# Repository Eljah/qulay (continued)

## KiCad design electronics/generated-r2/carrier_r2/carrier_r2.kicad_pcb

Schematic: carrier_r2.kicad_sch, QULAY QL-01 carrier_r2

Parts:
C1, C2, C3: 100n X7R; C0603
C4: 10u X7R 6.3V; C0603
J1: EXTERNAL_3V3_FUSED_1A; H2
J2: ENCODER_BANK_0; H6
J3: ENCODER_BANK_1; H6
J4: ENCODER_BANK_2; H6
J5: ENCODER_BANK_3; H6
J6: ADXL355_MODULE; H7
J7: ODOMETER_3V3_ONLY; H4
J8: ADC_BANK_FANOUT; H10
J9: INTERLOCK_GND_LIFT_PG_REMOTE_PULLUP; H4
Q1: MMBT3904; SOT23
R1, R2, R3, R4, R5, R6, R7, R8: 10k default-CS-high; R0603
R9, R11: 10k; R0603
R10, R13, R14: 100k; R0603
R12: 100k wire-open-low; R0603
R15, R16, R17, R18: 47R source termination; R0603
U1: Raspberry_Pi_Pico_USB_powered; PICO40
U2, U3: SN74LVC244APWR; TSSOP20
U4: SN74LVC125AD_IOFF; SOIC14

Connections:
ADC_CS0: J8.6 (ADC_CS0), R5.2 (ADC_CS0), U3.18 (ADC_CS0)
ADC_CS1: J8.7 (ADC_CS1), R6.2 (ADC_CS1), U3.16 (ADC_CS1)
ADC_CS2: J8.8 (ADC_CS2), R7.2 (ADC_CS2), U3.14 (ADC_CS2)
ADC_CS3: J8.9 (ADC_CS3), R8.2 (ADC_CS3), U3.12 (ADC_CS3)
ADC_MOSI: J8.4 (ADC_MOSI), R18.2 (ADC_MOSI)
ADC_MOSI_BUF: R18.1 (ADC_MOSI_BUF), U2.3 (ADC_MOSI_BUF)
ADC_SCK: J8.3 (ADC_SCK), R17.2 (ADC_SCK)
ADC_SCK_BUF: R17.1 (ADC_SCK_BUF), U2.5 (ADC_SCK_BUF)
CS0: J2.3 (CS0), R1.2 (CS0), U2.14 (CS0)
CS1: J3.3 (CS1), R2.2 (CS1), U2.12 (CS1)
CS2: J4.3 (CS2), R3.2 (CS2), U2.9 (CS2)
CS3: J5.3 (CS3), R4.2 (CS3), U2.7 (CS3)
CS_ADXL: J6.6 (CS_ADXL), U1.17 (CS_ADXL)
DRDY_ADXL: J6.7 (DRDY_ADXL), U1.19 (DRDY_ADXL)
GND: C1.2 (GND), C2.2 (GND), C3.2 (GND), C4.2 (GND), J1.2 (GND), J2.2 (GND), J3.2 (GND), J4.2 (GND), J5.2 (GND), J6.2 (GND), J7.2 (GND), J8.2 (GND), J8.10 (GND), J9.1 (GND), Q1.2 (GND), R10.2 (GND), R12.2 (GND), R13.2 (GND), R14.2 (GND), U1.3 (GND), U1.8 (GND), U1.13 (GND), U1.18 (GND), U1.23 (GND), U1.28 (GND), U1.33 (GND), U1.38 (GND), U2.10 (GND), U3.10 (GND), U3.11 (GND), U3.13 (GND), U3.15 (GND), U3.17 (GND), U4.1 (GND), U4.4 (GND), U4.7 (GND), U4.9 (GND), U4.12 (GND)
LIFT_STOWED_N: J9.2 (LIFT_STOWED_N), U1.26 (LIFT_STOWED_N)
MISO0: U1.6 (MISO0), U4.3 (MISO0)
MISO0_RAW: J2.6 (MISO0_RAW), J3.6 (MISO0_RAW), J4.6 (MISO0_RAW), J5.6 (MISO0_RAW), R13.1 (MISO0_RAW), U4.2 (MISO0_RAW)
MISO1: U1.16 (MISO1), U4.6 (MISO1)
MISO1_RAW: J6.5 (MISO1_RAW), J8.5 (MISO1_RAW), R14.1 (MISO1_RAW), U4.5 (MISO1_RAW)
MOSI0: J2.5 (MOSI0), J3.5 (MOSI0), J4.5 (MOSI0), J5.5 (MOSI0), R16.2 (MOSI0)
MOSI0_BUF: R16.1 (MOSI0_BUF), U2.16 (MOSI0_BUF)
ODO_A: J7.3 (ODO_A), U1.1 (ODO_A)
ODO_B: J7.4 (ODO_B), U1.2 (ODO_B)
OE_SENS_N: Q1.3 (OE_SENS_N), R11.2 (OE_SENS_N), U2.1 (OE_SENS_N), U2.19 (OE_SENS_N), U3.1 (OE_SENS_N), U3.19 (OE_SENS_N)
PICO_3V3: C3.1 (PICO_3V3), J6.1 (PICO_3V3), J7.1 (PICO_3V3), J9.4 (PICO_3V3), U1.36 (PICO_3V3), U4.10 (PICO_3V3), U4.13 (PICO_3V3), U4.14 (PICO_3V3)
POWER_GOOD: J9.3 (POWER_GOOD), R12.1 (POWER_GOOD), U1.27 (POWER_GOOD)
P_ADC_CS0: U1.21 (P_ADC_CS0), U3.2 (P_ADC_CS0)
P_ADC_CS1: U1.22 (P_ADC_CS1), U3.4 (P_ADC_CS1)
P_ADC_CS2: U1.24 (P_ADC_CS2), U3.6 (P_ADC_CS2)
P_ADC_CS3: U1.25 (P_ADC_CS3), U3.8 (P_ADC_CS3)
P_CS0: U1.7 (P_CS0), U2.6 (P_CS0)
P_CS1: U1.9 (P_CS1), U2.8 (P_CS1)
P_CS2: U1.10 (P_CS2), U2.11 (P_CS2)
P_CS3: U1.11 (P_CS3), U2.13 (P_CS3)
P_MOSI0: U1.5 (P_MOSI0), U2.4 (P_MOSI0)
P_MOSI1: J6.4 (P_MOSI1), U1.15 (P_MOSI1), U2.17 (P_MOSI1)
P_SCK0: U1.4 (P_SCK0), U2.2 (P_SCK0)
P_SCK1: J6.3 (P_SCK1), U1.14 (P_SCK1), U2.15 (P_SCK1)
Q_BASE: Q1.1 (Q_BASE), R9.2 (Q_BASE), R10.1 (Q_BASE)
SCK0: J2.4 (SCK0), J3.4 (SCK0), J4.4 (SCK0), J5.4 (SCK0), R15.2 (SCK0)
SCK0_BUF: R15.1 (SCK0_BUF), U2.18 (SCK0_BUF)
SENSOR_ENABLE: R9.1 (SENSOR_ENABLE), U1.29 (SENSOR_ENABLE)
SENS_3V3: C1.1 (SENS_3V3), C2.1 (SENS_3V3), C4.1 (SENS_3V3), J1.1 (SENS_3V3), J2.1 (SENS_3V3), J3.1 (SENS_3V3), J4.1 (SENS_3V3), J5.1 (SENS_3V3), J8.1 (SENS_3V3), R1.1 (SENS_3V3), R2.1 (SENS_3V3), R3.1 (SENS_3V3), R4.1 (SENS_3V3), R5.1 (SENS_3V3), R6.1 (SENS_3V3), R7.1 (SENS_3V3), R8.1 (SENS_3V3), R11.1 (SENS_3V3), U2.20 (SENS_3V3), U3.20 (SENS_3V3)

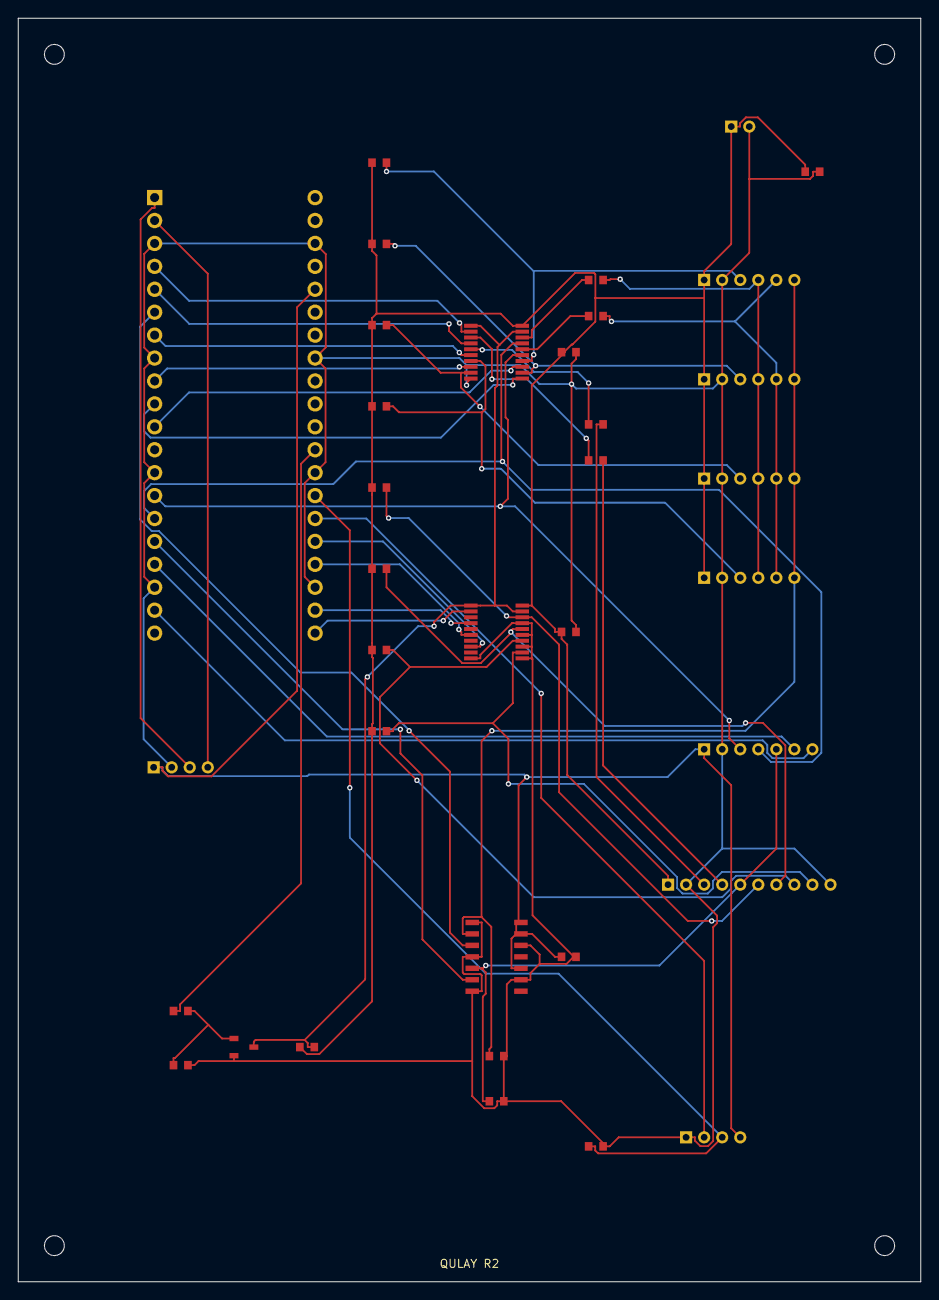
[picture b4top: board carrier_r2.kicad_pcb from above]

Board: 2 copper layers, 100.0 x 140.0 mm, 40 parts (0 on the bottom side), 44 nets.

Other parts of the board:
MH1, MH2, MH3, MH4: MountingHole_2.2mm

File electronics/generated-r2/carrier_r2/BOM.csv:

reference,value,footprint,quantity_per_board
U1,Raspberry_Pi_Pico_USB_powered,PICO40,1
J1,EXTERNAL_3V3_FUSED_1A,H2,1
U2,SN74LVC244APWR,TSSOP20,1
U3,SN74LVC244APWR,TSSOP20,1
U4,SN74LVC125AD_IOFF,SOIC14,1
C1,100n X7R,C0603,1
C2,100n X7R,C0603,1
C3,100n X7R,C0603,1
C4,10u X7R 6.3V,C0603,1
J2,ENCODER_BANK_0,H6,1
J3,ENCODER_BANK_1,H6,1
J4,ENCODER_BANK_2,H6,1
J5,ENCODER_BANK_3,H6,1
J6,ADXL355_MODULE,H7,1
J7,ODOMETER_3V3_ONLY,H4,1
J8,ADC_BANK_FANOUT,H10,1
J9,INTERLOCK_GND_LIFT_PG_REMOTE_PULLUP,H4,1
R1,10k default-CS-high,R0603,1
R2,10k default-CS-high,R0603,1
R3,10k default-CS-high,R0603,1
R4,10k default-CS-high,R0603,1
R5,10k default-CS-high,R0603,1
R6,10k default-CS-high,R0603,1
R7,10k default-CS-high,R0603,1
R8,10k default-CS-high,R0603,1
Q1,MMBT3904,SOT23,1
R9,10k,R0603,1
R10,100k,R0603,1
R11,10k,R0603,1
R12,100k wire-open-low,R0603,1
R13,100k,R0603,1
R14,100k,R0603,1
R15,47R source termination,R0603,1
R16,47R source termination,R0603,1
R17,47R source termination,R0603,1
R18,47R source termination,R0603,1

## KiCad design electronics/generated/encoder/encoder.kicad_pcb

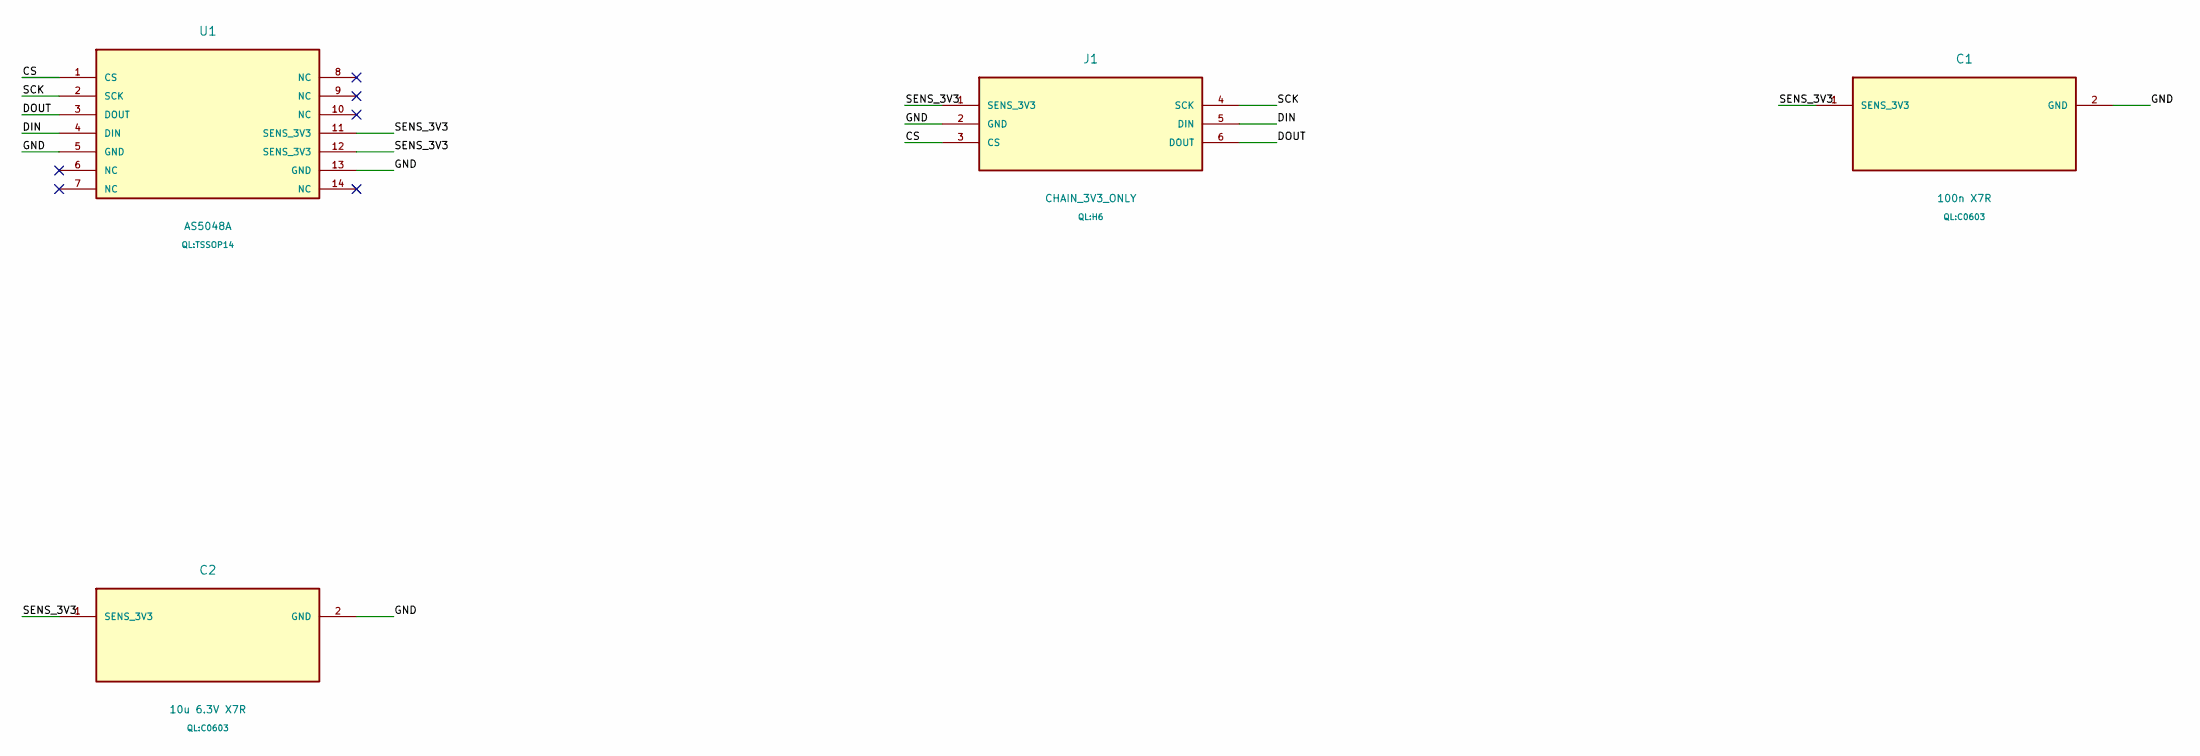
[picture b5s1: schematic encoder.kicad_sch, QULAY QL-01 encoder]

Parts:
C1: 100n X7R; C0603
C2: 10u 6.3V X7R; C0603
J1: CHAIN_3V3_ONLY; H6
U1: AS5048A; TSSOP14

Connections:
CS: J1.3 (CS), U1.1 (CS)
DIN: J1.5 (DIN), U1.4 (DIN)
DOUT: J1.6 (DOUT), U1.3 (DOUT)
GND: C1.2 (GND), C2.2 (GND), J1.2 (GND), U1.5 (GND), U1.13 (GND)
SCK: J1.4 (SCK), U1.2 (SCK)
SENS_3V3: C1.1 (SENS_3V3), C2.1 (SENS_3V3), J1.1 (SENS_3V3), U1.11 (SENS_3V3), U1.12 (SENS_3V3)

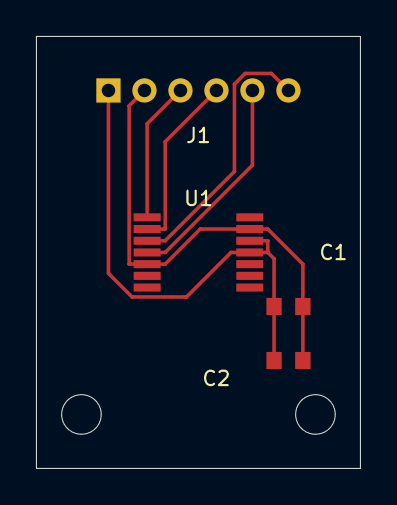
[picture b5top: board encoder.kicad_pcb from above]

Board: 2 copper layers, 18.0 x 24.0 mm, 6 parts (0 on the bottom side), 6 nets.

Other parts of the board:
MH1, MH2: MountingHole_2.2mm

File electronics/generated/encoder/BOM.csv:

reference,value,footprint,quantity_per_board
U1,AS5048A,TSSOP14,1
J1,CHAIN_3V3_ONLY,H6,1
C1,100n X7R,C0603,1
C2,10u 6.3V X7R,C0603,1

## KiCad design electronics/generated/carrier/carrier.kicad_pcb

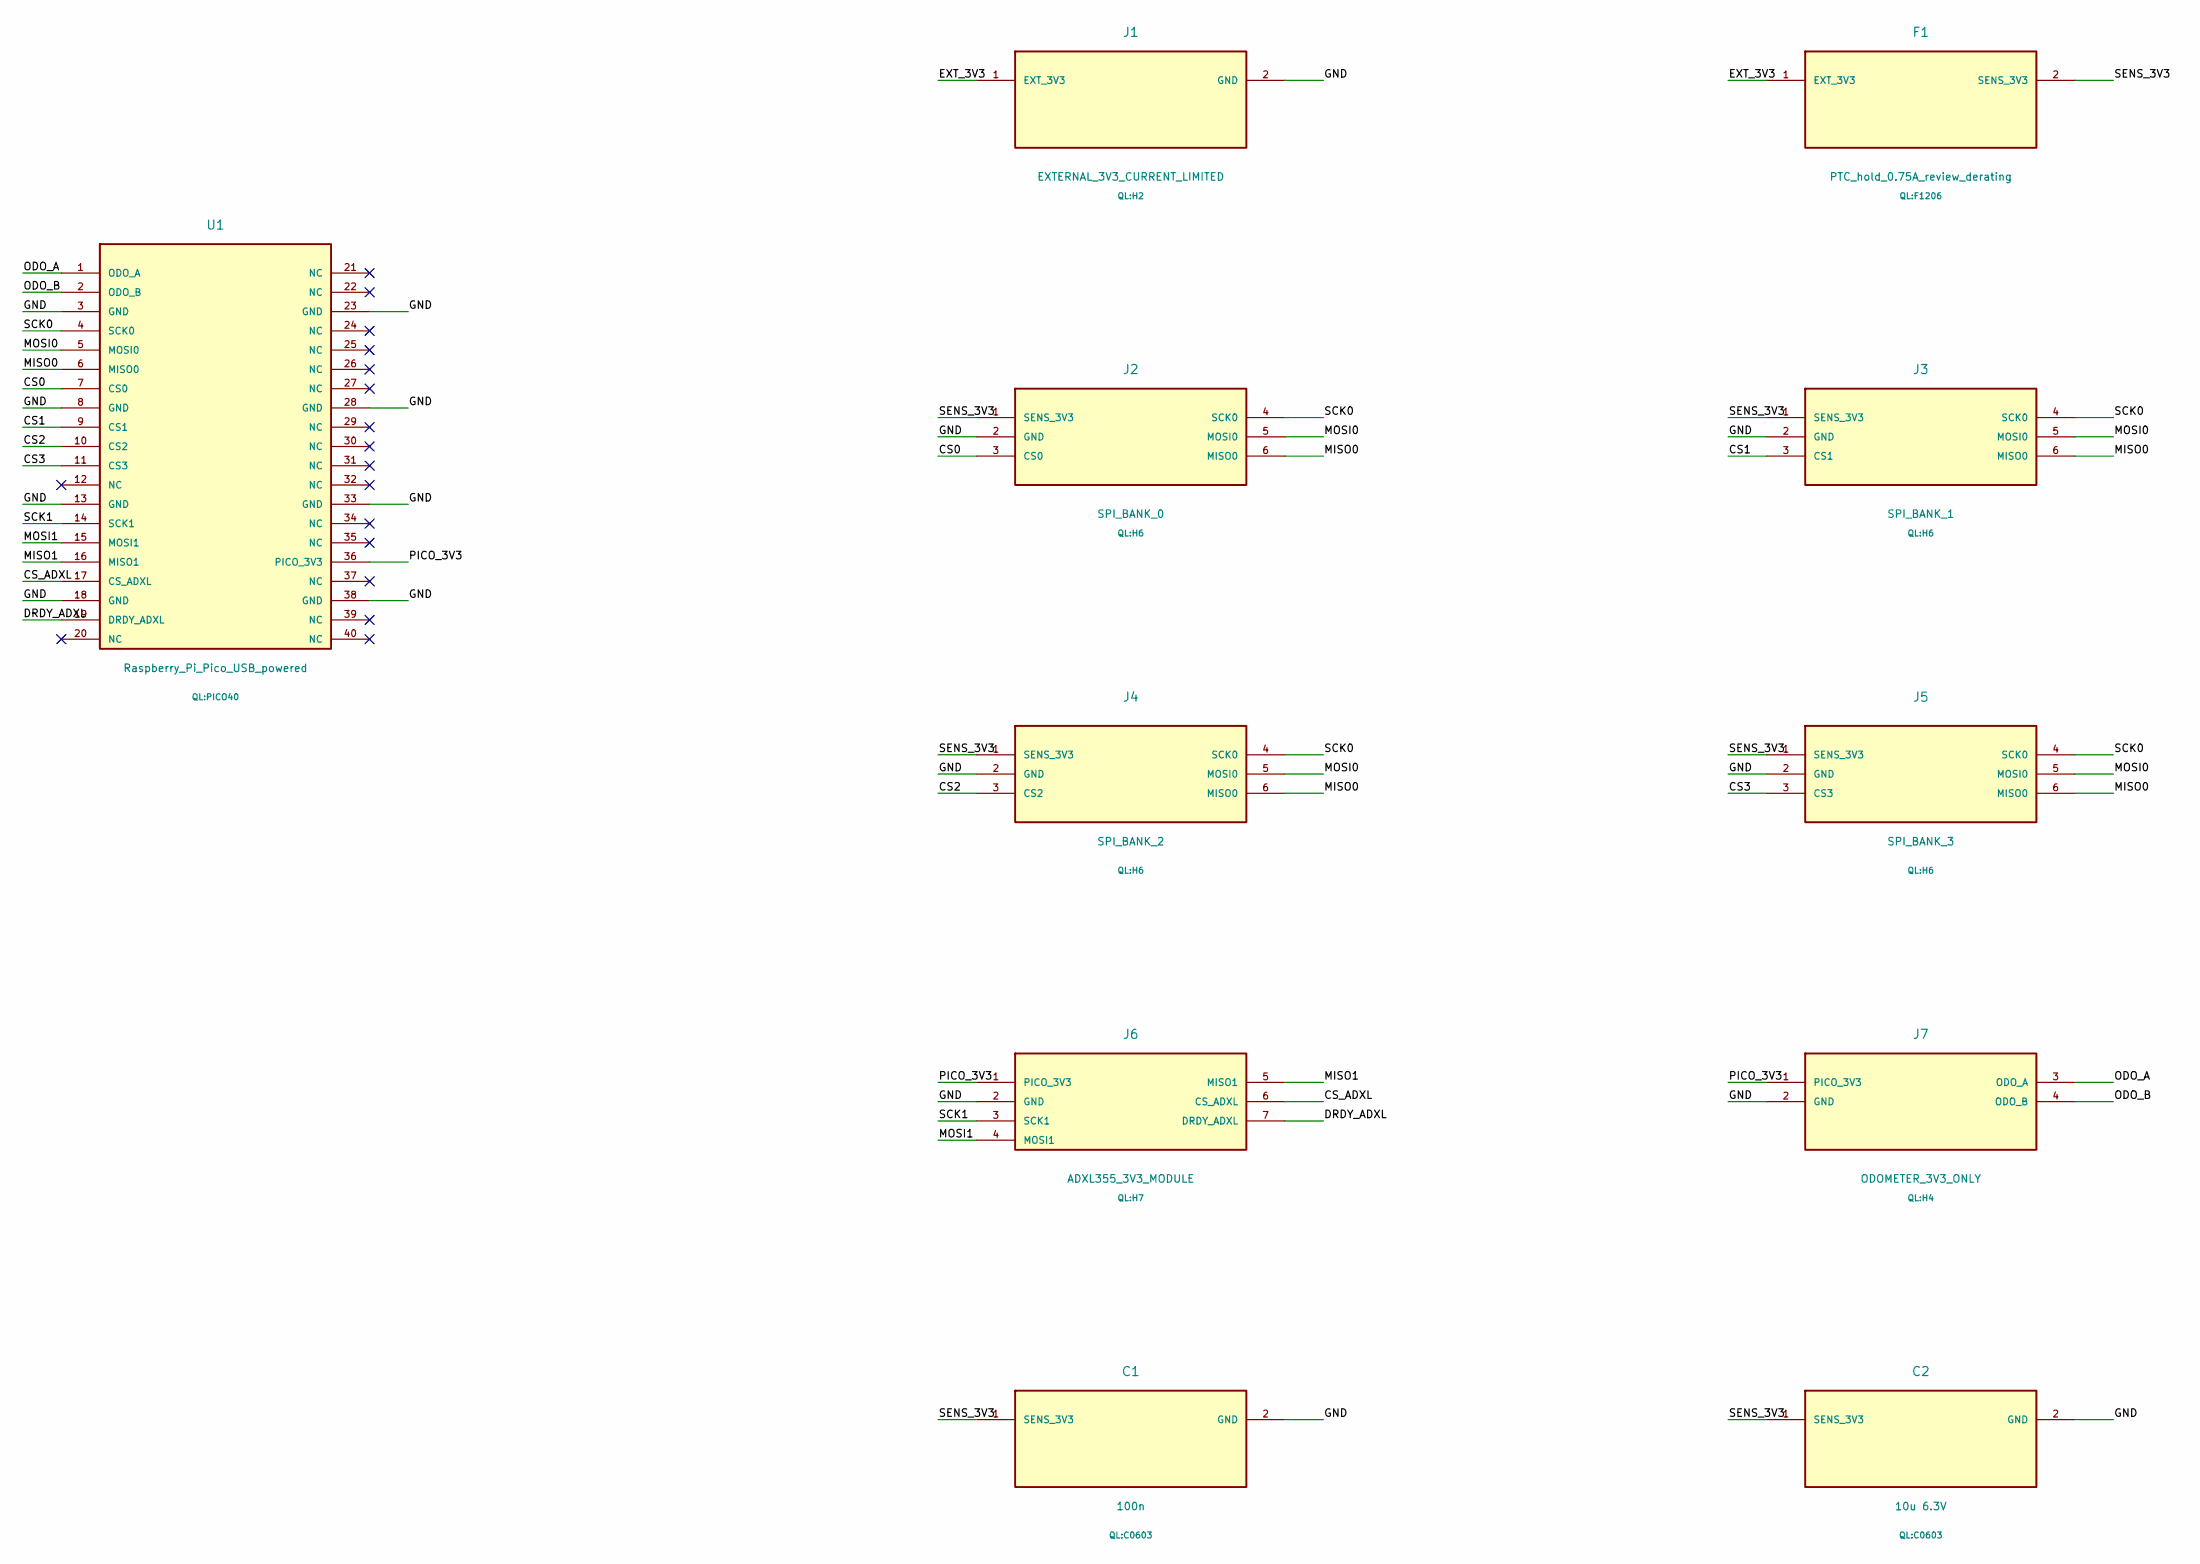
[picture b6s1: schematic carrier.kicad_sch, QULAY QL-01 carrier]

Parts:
C1: 100n; C0603
C2: 10u 6.3V; C0603
F1: PTC_hold_0.75A_review_derating; F1206
J1: EXTERNAL_3V3_CURRENT_LIMITED; H2
J2: SPI_BANK_0; H6
J3: SPI_BANK_1; H6
J4: SPI_BANK_2; H6
J5: SPI_BANK_3; H6
J6: ADXL355_3V3_MODULE; H7
J7: ODOMETER_3V3_ONLY; H4
U1: Raspberry_Pi_Pico_USB_powered; PICO40

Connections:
CS0: J2.3 (CS0), U1.7 (CS0)
CS1: J3.3 (CS1), U1.9 (CS1)
CS2: J4.3 (CS2), U1.10 (CS2)
CS3: J5.3 (CS3), U1.11 (CS3)
CS_ADXL: J6.6 (CS_ADXL), U1.17 (CS_ADXL)
DRDY_ADXL: J6.7 (DRDY_ADXL), U1.19 (DRDY_ADXL)
EXT_3V3: F1.1 (EXT_3V3), J1.1 (EXT_3V3)
GND: C1.2 (GND), C2.2 (GND), J1.2 (GND), J2.2 (GND), J3.2 (GND), J4.2 (GND), J5.2 (GND), J6.2 (GND), J7.2 (GND), U1.3 (GND), U1.8 (GND), U1.13 (GND), U1.18 (GND), U1.23 (GND), U1.28 (GND), U1.33 (GND), U1.38 (GND)
MISO0: J2.6 (MISO0), J3.6 (MISO0), J4.6 (MISO0), J5.6 (MISO0), U1.6 (MISO0)
MISO1: J6.5 (MISO1), U1.16 (MISO1)
MOSI0: J2.5 (MOSI0), J3.5 (MOSI0), J4.5 (MOSI0), J5.5 (MOSI0), U1.5 (MOSI0)
MOSI1: J6.4 (MOSI1), U1.15 (MOSI1)
ODO_A: J7.3 (ODO_A), U1.1 (ODO_A)
ODO_B: J7.4 (ODO_B), U1.2 (ODO_B)
PICO_3V3: J6.1 (PICO_3V3), J7.1 (PICO_3V3), U1.36 (PICO_3V3)
SCK0: J2.4 (SCK0), J3.4 (SCK0), J4.4 (SCK0), J5.4 (SCK0), U1.4 (SCK0)
SCK1: J6.3 (SCK1), U1.14 (SCK1)
SENS_3V3: C1.1 (SENS_3V3), C2.1 (SENS_3V3), F1.2 (SENS_3V3), J2.1 (SENS_3V3), J3.1 (SENS_3V3), J4.1 (SENS_3V3), J5.1 (SENS_3V3)

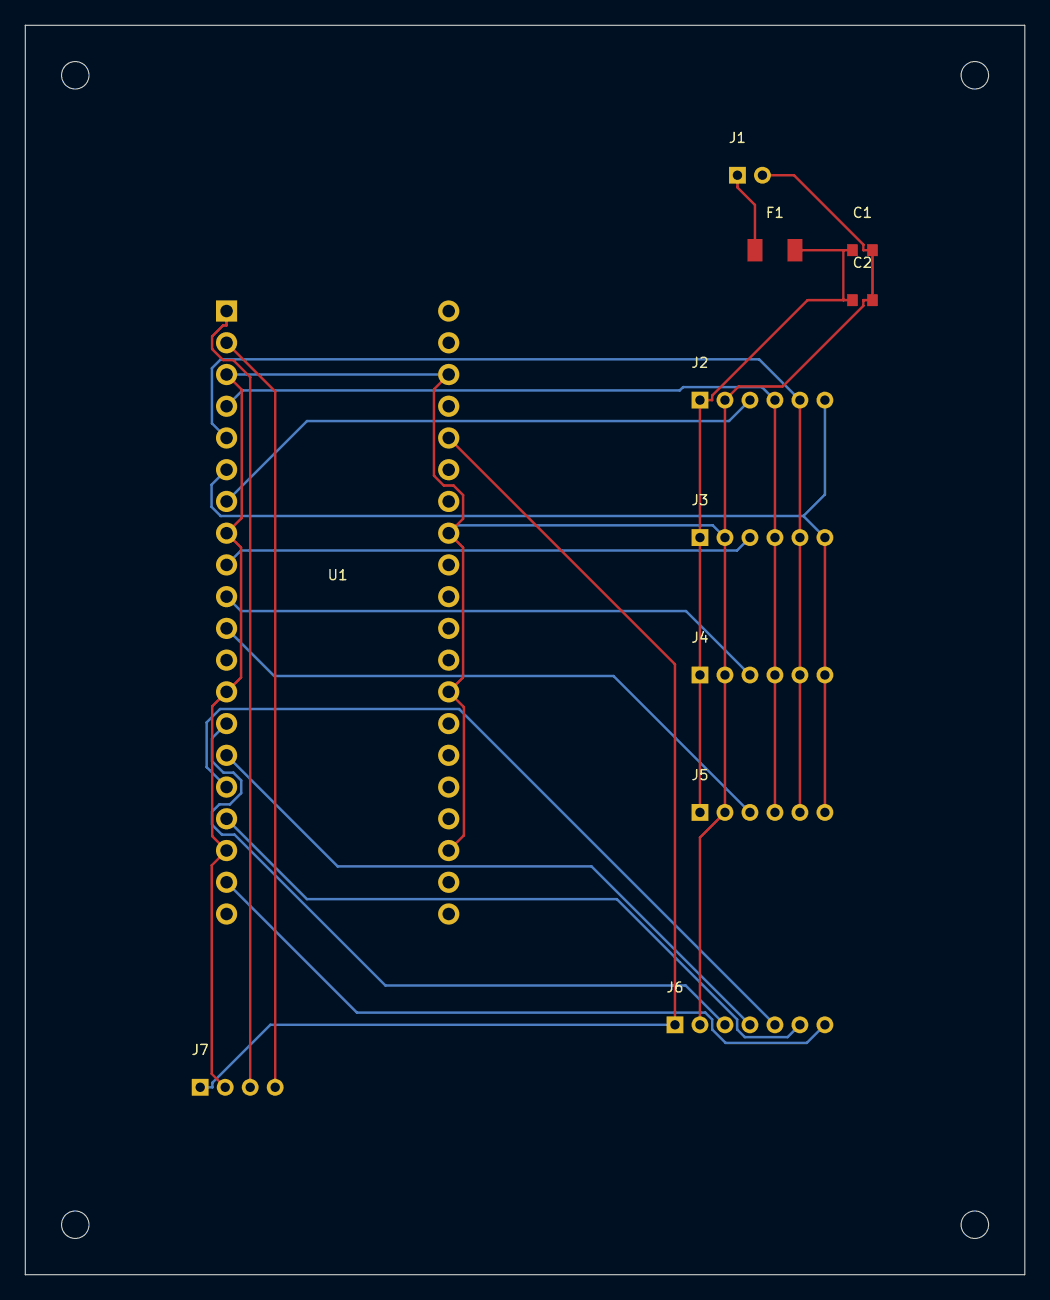
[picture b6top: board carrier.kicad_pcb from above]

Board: 2 copper layers, 80.0 x 100.0 mm, 15 parts (0 on the bottom side), 18 nets.

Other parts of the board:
MH1, MH2, MH3, MH4: MountingHole_2.2mm

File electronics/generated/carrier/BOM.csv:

reference,value,footprint,quantity_per_board
U1,Raspberry_Pi_Pico_USB_powered,PICO40,1
J1,EXTERNAL_3V3_CURRENT_LIMITED,H2,1
F1,PTC_hold_0.75A_review_derating,F1206,1
J2,SPI_BANK_0,H6,1
J3,SPI_BANK_1,H6,1
J4,SPI_BANK_2,H6,1
J5,SPI_BANK_3,H6,1
J6,ADXL355_3V3_MODULE,H7,1
J7,ODOMETER_3V3_ONLY,H4,1
C1,100n,C0603,1
C2,10u 6.3V,C0603,1

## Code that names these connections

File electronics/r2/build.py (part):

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def cap(ref,xy,net='SENS_3V3',value='100n X7R'):return part(ref,value,'C0603',xy,{'1':net,'2':'GND'})
def resistor(ref,xy,n1,n2,value):return part(ref,value,'R0603',xy,{'1':n1,'2':n2})
def gate244(ref,xy,pairs):
    pins={'1':'OE_SENS_N','10':'GND','19':'OE_SENS_N','20':'SENS_3V3'};types={'1':'input','19':'input','10':'power_in','20':'power_in'}
    for (a,y),(inn,out) in zip([(2,18),(4,16),(6,14),(8,12),(11,9),(13,7),(15,5),(17,3)],pairs):
        pins[str(a)]=inn;pins[str(y)]=out;types[str(a)]='input';types[str(y)]='tri_state'
    return part(ref,'SN74LVC244APWR','TSSOP20',xy,dict(sorted(pins.items(),key=lambda it:int(it[0]))),types)
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if __name__=='__main__':
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    generate('force',force,(18,12),[(2,2),(16,10)])
    pins={str(i+1):'A'+str(i) for i in range(8)};pins.update({'9':'GND','10':'ADC_CS','11':'ADC_MOSI','12':'ADC_OUT_RAW','13':'ADC_SCK','14':'GND','15':'SENS_3V3','16':'SENS_3V3'})
    types={'9':'power_in','10':'input','11':'input','12':'tri_state','13':'input','14':'power_in','15':'power_in','16':'power_in'}
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    adc.extend([cap('C1',(34,23)),cap('C2',(34,27),value='10u X7R 6.3V'),part('U2','SN74LVC1G125DBVR_IOFF','SOT23_5',(60,38),{'1':'ADC_CS','2':'ADC_OUT_RAW','3':'GND','4':'ADC_MISO','5':'SENS_3V3'},{'1':'input','2':'input','3':'power_in','4':'tri_state','5':'power_in'}),cap('C3',(55,38))])
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
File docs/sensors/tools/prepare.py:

"""Read real KiCad/CAD/code inputs; generate channel tables and a non-qualified example.
No manufacturing approval or physical test is implied by this document build.
"""
from pathlib import Path
import csv, json, re, math, hashlib
ROOT=Path(__file__).resolve().parents[3]
OUT=ROOT/'docs/sensors/generated';OUT.mkdir(parents=True,exist_ok=True)
BASE='097e60be99069dc5490a207dd999f34820637a1a'

def sexp(text):
    tokens=re.findall(r'\(|\)|"(?:\\.|[^"\\])*"|[^\s()]+',text)
    stack=[]; root=None
    for t in tokens:
        if t=='(':
            v=[]
            if stack:stack[-1].append(v)
            else:root=v
            stack.append(v)
        elif t==')':stack.pop()
        else:
            stack[-1].append(json.loads(t) if t.startswith('"') else t)
    if stack or root is None:raise ValueError('Invalid S-expression')
    return root

def child(x,key,default=None):
    return next((n for n in x if isinstance(n,list) and n and n[0]==key),default)

def pcb(rel):
    r=sexp((ROOT/rel).read_text());out={}
    for f in r:
        if not isinstance(f,list) or not f or f[0]!='footprint':continue
        ref=next((n[2] for n in f if isinstance(n,list) and n[:2]==['property','Reference']),None)
        if ref is None:
            z=next((n for n in f if isinstance(n,list) and n[:2]==['fp_text','reference']),None)
            ref=z[2] if z else '?'
        a=child(f,'at');x,y=map(float,a[1:3]);rot=float(a[3]) if len(a)>3 else 0
        pads=[]
        for pad in f:
            if not isinstance(pad,list) or not pad or pad[0]!='pad':continue
            t=child(pad,'at');dx,dy=map(float,t[1:3]);s=child(pad,'size');net=child(pad,'net')
            rr=math.radians(rot)
            pads.append({'pin':pad[1],'u':x+dx*math.cos(rr)+dy*math.sin(rr),'v':y-dx*math.sin(rr)+dy*math.cos(rr),'width':float(s[1]),'height':float(s[2]),'net':net[2] if net else ''})
        out[ref]={'u':x,'v':y,'rotation_deg':rot,'pads':pads,'library':f[1]}
    return out

def connections(rel):
    return {(r['reference'],r['pin']):r['net'] for r in csv.DictReader((ROOT/rel).open())}

def writecsv(name,fields,rows):
    with (OUT/name).open('w',encoding='utf-8-sig',newline='') as f:
        w=csv.DictWriter(f,fieldnames=fields);w.writeheader();w.writerows(rows)

paths={
 'encoder_pcb':'electronics/generated/encoder/encoder.kicad_pcb',
 'encoder_nets':'electronics/generated/encoder/connections.csv',
 'r1_pcb':'electronics/generated/carrier/carrier.kicad_pcb',
 'r1_nets':'electronics/generated/carrier/connections.csv',
 'r2_pcb':'electronics/generated-r2/carrier_r2/carrier_r2.kicad_pcb',
 'r2_nets':'electronics/generated-r2/carrier_r2/connections.csv',
 'force_nets':'electronics/generated-r2/force/connections.csv',
 'adc_nets':'electronics/generated-r2/adc/connections.csv',
 'harness':'electronics/generated/harness.csv',
 'cad':'mechanical/revision_b.py','coupling':'mechanical/coupling_c1/build.py',
 'coupling_note':'mechanical/coupling_c1/README.md',
 'image':'mechanical/coupling_c1/generated/exploded.png',
 'channel_image':'docs/channel/assets/single-channel.png',
 'q1':'firmware/src/main.c','q2':'firmware/r2/main.c','protocol':'firmware/include/protocol.h',
 'model':'software/core/src/main/java/org/qulay/core/Model.java',
 'geometry':'software/core/src/main/java/org/qulay/core/Geometry.java',
 'contact':'software/core/src/main/java/org/qulay/core/ContactModel.java',
 'wire':'software/agent/src/main/java/org/qulay/agent/Wire.java',
 'wire2':'software/agent/src/main/java/org/qulay/agent/WireV2.java',
 'agent':'software/agent/src/main/java/org/qulay/agent/Agent.java',
 'json':'software/core/src/main/java/org/qulay/core/Json.java',
 'desktop':'software/desktop/src/main/java/org/qulay/desktop/DesktopApp.java'
}

def main():
    manifest={k:{'path':v,'sha256':hashlib.sha256((ROOT/v).read_bytes()).hexdigest(),'git_blob':hashlib.sha1(b'blob '+str((ROOT/v).stat().st_size).encode()+b'\0'+(ROOT/v).read_bytes()).hexdigest()} for k,v in paths.items()}
    boards={key:pcb(paths[key+'_pcb']) for key in ['encoder','r1','r2']}
    ns=connections(paths['encoder_nets'])
    expected={'1':'CS','2':'SCK','3':'DOUT','4':'DIN','5':'GND','6':'NC','7':'NC','8':'NC','9':'NC','10':'NC','11':'SENS_3V3','12':'SENS_3V3','13':'GND','14':'NC'}
    assert all(ns['U1',k]==v for k,v in expected.items())
    assert all(ns['J1',str(i)]==v for i,v in enumerate(['SENS_3V3','GND','CS','SCK','DIN','DOUT'],1))
    pin1=next(p for p in boards['encoder']['U1']['pads'] if p['pin']=='1')
    assert abs(pin1['u']-6.15)<1e-5 and abs(pin1['v']-10.05)<1e-5
    j1=boards['encoder']['J1']['pads'];assert len(j1)==6
    for p in j1:assert abs(p['u']-(4+2*(int(p['pin'])-1)))<1e-5 and abs(p['v']-3)<1e-5
    maps=[];wire=[]
    source_harness=list(csv.DictReader((ROOT/paths['harness']).open()))
    original={(int(x['channel']),int(x['sensor_pin'])):x['connect_to'] for x in source_harness}
    for j in range(31):
        b,k=divmod(j,8);n=[8,8,8,7][b];cs=[5,6,7,8][b];physical=[7,9,10,11][b]
        row={'java_index':j,'cad_suffix':f'{j+1:02d}','encoder_label':f'encoder{j:02d}','Y_mm':(j-15)*25,'bank':b,'slot':k,'bank_size':n,'carrier_connector':f'J{b+2}','CS_gpio':cs,'CS_physical_pin':physical,'r2_adc_bank':b,'r2_adc_channel':k,'r2_adc_J2_OUT_pin':3*k+3}
        maps.append(row)
        dest=[f'carrier.J{b+2}.1',f'carrier.J{b+2}.2',f'carrier.J{b+2}.3',f'carrier.J{b+2}.4',f'carrier.J{b+2}.5' if k==0 else f'encoder{j-1:02d}.J1.6',f'carrier.J{b+2}.6' if k==n-1 else f'encoder{j+1:02d}.J1.5']
        for pin,(signal,to) in enumerate(zip(['SENS_3V3','GND','CSn','SCK','DIN','DOUT'],dest),1):
            assert original[j,pin]==to,(j,pin,to,original[j,pin])
            wire.append({'label':f'G{b}-E{j:02d}-P{pin}','from':f'encoder{j:02d}.J1.{pin}','signal':signal,'to':to,'note':'4 common conductors; data is daisy-chained, not parallel'})
    assert len(maps)==31 and len(wire)==186
    for key in ['r1','r2']:
        net=connections(paths[key+'_nets'])
        for b in range(4):
            for pin,sig in [(1,'SENS_3V3'),(2,'GND'),(3,f'CS{b}')]:assert net[f'J{b+2}',str(pin)]==sig
        assert net['J6','1']=='PICO_3V3' and net['J6','2']=='GND'
    orientation={'standard_top_U1_pin1_uv_mm':[pin1['u'],pin1['v']], 'front_transform':'X=9-u; Z-H=v-12; F.Cu faces -Y', 'mounted_front_J1_left_to_right':[6,5,4,3,2,1], 'mounted_back_J1_left_to_right':[1,2,3,4,5,6], 'scope':'Derived coordinate placement; actual connector body and lead dress require mechanical clearance check.'}
    writecsv('channel-map.csv',list(maps[0]),maps);writecsv('encoder-harness.csv',list(wire[0]),wire)
    blank=[dict(j=j,bank=j//8,slot=j%8,cad=f'{j+1:02d}',serial='',sign_checked='',raw_reference='',reference_angle_deg='',zero_rad='',lut_id='',operator='',date='') for j in range(31)]
    writecsv('commissioning-31-channels.csv',list(blank[0]),blank)
    cal={'id':'SENSOR-GUIDE-DEMO-NOT-FOR-HARDWARE','traceable':False,'odometerMmPerTick':0.1,'expandedHeightUncertaintyMm':2.0,'expandedGradeUncertainty':0.005,'channels':[]}
    for j in range(31):
        ch={'pivotXmm':0,'pivotYmm':(j-15)*25,'pivotZmm':0,'lengthMm':240,'radiusMm':20,'zeroRad':0,'measuredRad':[],'correctedRad':[],'contact':None}
        if j==8:
            ch['zeroRad']=-math.pi/2
            ch['measuredRad']=[x*2*math.pi/16384-math.pi/2 for x in [1365,2048,2731]]
            ch['correctedRad']=[math.radians(x) for x in [-60,-45,-30]]
        cal['channels'].append(ch)
    (OUT/'calibration-DEMO.json').write_text(json.dumps(cal,ensure_ascii=False,indent=2)+'\n')
    data={'engineering_baseline':BASE,'paths':paths,'manifest':manifest,'boards':boards,'channels':maps,'orientation':orientation,'checks':{'AS5048_pin_to_net':True,'encoder_pad_positions':True,'31_channels':True,'186_harness_endpoints_match_repository':True,'r1_r2_connector_pin_functions':True,'physical_test':False}}
    (OUT/'engineering-data.json').write_text(json.dumps(data,ensure_ascii=False,indent=2))
    (OUT/'source-manifest.json').write_text(json.dumps({'baseline':BASE,'files':manifest,'physical_tests':False},indent=2))
    print(json.dumps(data['checks'],indent=2))
if __name__=='__main__':main()
